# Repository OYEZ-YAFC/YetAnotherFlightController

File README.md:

# YetAnotherFlightController

Repository for the YAFC project at Université Toulouse III - Paul Sabatier, 2022-2023, Master 1 Computer Science Embedded Systems.

## Authors / Contact :

- Oussama Felfel - oussama.felfel@univ-tlse3.fr

- Yasmine Benhaddou - yasmine.benhaddou@univ-tlse3.fr

- Elana Courtines - elana.courtines@univ-tlse3.fr

- Zineb Moubarik - zineb.moubarik@univ-tlse3.fr

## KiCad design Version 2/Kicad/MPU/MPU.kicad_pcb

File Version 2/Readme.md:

# How to Setup Betaflight Firmware

----------------------------------------------------------------------------------------------------------------
## 1.Install Betaflight Configurator

### Installation & Documentation
See: https://betaflight.com/docs/wiki

### Configuration Tool
To configure Betaflight you should use the Betaflight-configurator GUI tool (Windows/OSX/Linux) which can be found here:

https://github.com/betaflight/betaflight-configurator/releases/latest
---------------------------------------------------------------------------------------------------------------

## 2.Update Firmware

Flashing the FC consists of updating it so that it can have the latest software version from the constructor.

Before performing any manipulation on your fpv drone, you must save the original data of your drone. Indeed, if you have made a bad manipulation on the configuration, you just have to go back to this basic version of your configuration.

To perform the update, you must be in DFU (bootloader) mode. To do this, go to the “CLI” and tape : version, it will show us which target we should install. After that tape the command : diff,  by using this command, you can easily see the changes you have made to your drone's configuration and compare them to a previous working configuration. This can be useful for troubleshooting configuration issues or for optimizing your drone's performance.

the last step, is to be able to flash the firmware, you will have to restart in DFU mode (bootloader).
It is also possible to launch this mode by pressing the physical button of the FC and unplugging and replugging the USB cable.

Thereafter, => click “Flash Firmware” on Betaflight’s left navigation bar.

=> disable “Show release candidates” 
=> choose the model of your card.
=> select the latest available version of your FC.
Then it remains to click on “Load firmware [Online]”.

----------------------------------------------------------------------------------------------------------------
## 3.Configure Betaflight For The First Time
----------------------------------------------------------------------------------------------------------------
##   3.1.Connect FC to Computer

----------------------------------------------------------------------------------------------------------------
##   3.2.Setup

The “Setup” tab allows you to calibrate the accelerometer of your flight controller.

An accelerometer measures the linear acceleration of the drone on 3 axes (X/Y/Z). As a result, you will be able to know if your drone is moving on one of these three axes.

To calibrate your accelerometer, you must position your chassis flat, and click on the “calibrate” button. Make sure that it is of course a flat surface and that nothing moves during the calibration.

----------------------------------------------------------------------------------------------------------------
##   3.3.Port

At this stage, you have several options:

- Assign a receiver (Rx) to a UART: in the “Serial Rx” column, check the small button (it should turn yellow). If your receiver is on UART 4 (Tx 4 and Rx 4 on your FC), you need to go to the line of UART 4 (on Betablight).
- Declare a 4-in-1 ESC to a UART (individual ESCs do not need to be assigned): in the “Sensor Input” column, choose ESC.
- Assign a VTX to a UART.
- Declare a GPS to an UART (if you have one): always in the “Sensor input” column, choose GPS.

----------------------------------------------------------------------------------------------------------------

##   3.4.Configuration

In this part of Betaflight, you will be able to configure a major part of your multirotor (ESC etc…). For this, you have a multitude of fields to complete:
“System configuration” field:

“Gyro update frequency”: this value is blocked, no need to take care of it
“PID loop frequency”: leave the original value
Disable or enable the “barometer” if your HR has it
Disable “magnetometer”

“Other features” field:

TELEMETRY: activating telemetry will allow you to retrieve information from the sensors of your Flight Controller on the remote control
AIRMODE: the airmode must be activated since it allows your drone to keep the same trajectory when you let go of the controls. This prevents it from doing 360s when you let go of the controls.
OSD: this feature must be activated to have the information in your glasses or your FPV mask

“ESC/Motor Features” field:

“ESC/motor protocol”: This is the language used to communicate from the ESC to the FC. I invite you to see the ESC product sheet. OneShot and MultiShot protocols are older compared to Dshot protocol. If you have Dshot, I invite you to choose the Dshot300 or Dshot600. If you choose higher, you risk “burning” your ESC. In the situation where your ESCs do not have this protocol, fall back on OneShot125 or even Multishot

“Arming” field:

“Maximum angle to arm“: this value must be “180°”, this will allow you to take off your drone in the situation where it is stuck on a branch at 90 degrees from the ground.

----------------------------------------------------------------------------------------------------------------
##   3.5. Power & battery
Betaflight can report the current LiPo status to the pilot, and whether or not he can continue to fly. To do this, go to the “Power and battery” tab and configure:

The “Battery” field:

“Minimum voltage per cell”: 3.75 Volt per cell, once you have reached this battery level, you must land to preserve your battery.
“Maximum voltage per element”: 4.2 Volt per cell.
“Warning voltage per cell”: 3.70 Volt per cell. Going below this value can irreversibly damage your LiPo!

----------------------------------------------------------------------------------------------------------------
##   3.6.Voltage Calibration

----------------------------------------------------------------------------------------------------------------
##   3.7.Receiver

----------------------------------------------------------------------------------------------------------------
##   3.8.Modes 

I advise you to activate the following modes:

- PREARM: the prearm constitutes an additional security for arming (activating) the motors. In the situation where you accidentally cock your drone in your hands. It can save you from unnecessary injuries.
- ARM: arming your drone consists of activating the drone's motors
- HORIZON: for beginners, this mode allows the drone to be stabilized if necessary
- BEEPER: ring the buzzer (if you have one)
- GPS RESCUE: activate the GPS (if you have one)
To do this, you must choose an “AUX” and slide the rightmost or leftmost range selector.

----------------------------------------------------------------------------------------------------------------
##   3.9.Motors

You must test your motors one by one and you have to use the white slider to spin the motor and see if there is an error. Raise this value slightly (to 1050 or 1100), there is no point in raising it too high except overheating your components.

This is also an opportunity to check if the correct motor is running. For example, if you run motor 1, motor 1 is running and so on...

----------------------------------------------------------------------------------------------------------------
##   3.10.OSD

----------------------------------------------------------------------------------------------------------------
##   3.11.PID Tuning

----------------------------------------------------------------------------------------------------------------
##   3.12.Video Transmitter

----------------------------------------------------------------------------------------------------------------
##   3.13.Expert Mode

----------------------------------------------------------------------------------------------------------------
##   3.14.Stop Beeping on the Bench

----------------------------------------------------------------------------------------------------------------
##   3.15.Safety Checks Before Maiden Flight

----------------------------------------------------------------------------------------------------------------

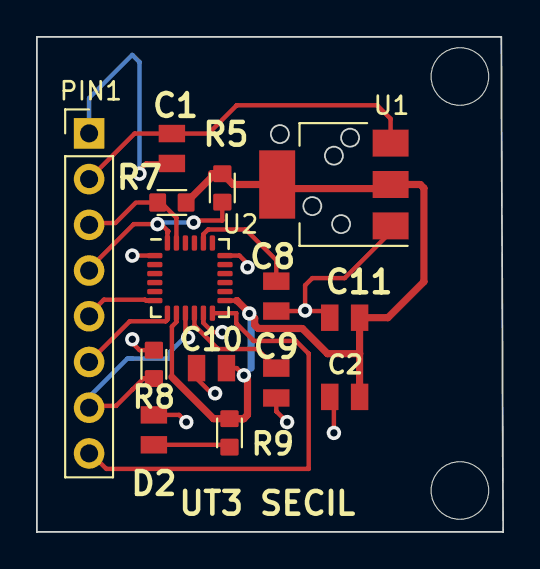
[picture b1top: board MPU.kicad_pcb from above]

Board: 2 copper layers, 25.9 x 27.5 mm, 14 parts (0 on the bottom side), 12 nets.

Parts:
C1: 4.7uF; CAPC2012X145N
C2: 10uF; CAPC2012X145N
C8: 2.2uF; CAPC2012X145N
C9, C10, C11: 100nF; CAPC2012X145N
D2: LED; CAPC2012X145N
PIN1: Conn_01x08; PinHeader_1x08_P2.54mm_Vertical
R5, R7, R8: 4.7k; RESC1608X50N
R9: 1k; RESC1608X50N
U1: AMS1117-3.3; SOT-223-3_TabPin2
U2: MPU-6050; InvenSense_QFN-24_4x4mm_P0.5mm

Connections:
+3.3V: C2.2, C10.2, C11.2, R5.1, R7.1, R9.1, U1.2 (VO), U2.8 (VLOGIC), U2.13 (VDD)
/AD0: PIN1.7, R8.2, U2.9 (AD0)
/INT: PIN1.8, U2.12 (INT)
/SCL: PIN1.3, R7.2, U2.23 (SCL)
/SDA: PIN1.4, R5.2, U2.24 (SDA)
/XCL: PIN1.6, U2.7 (AUX_CL)
/XDA: PIN1.5, U2.6 (AUX_DA)
GND: C1.1, C2.1, C8.2, C9.1, C10.1, C11.1, D2.1 (K), PIN1.1, R8.1, U1.1 (GND), U2.1 (CLKIN), U2.11 (FSYNC), U2.18 (GND)
unnamed: D2.2 (A), R9.2
unnamed: C8.1, U2.20 (CPOUT)
unnamed: C9.2, U2.10 (REGOUT)
VCC: C1.2, PIN1.2, U1.3 (VI)

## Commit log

2022-11-30 Updated: README.md - added authors
2022-11-30 Added: tex file for the kickoff
2022-11-30 Updated: Kickoff meeting presentation
    The kickoff meeting latex file has been updated. It is ready for the meeting.
2022-12-01 Updated: Kickoff presentation
    Both the LaTeX and the PDF files now reflect the most recent changes.
2022-12-05 Removed: Deliverable files have been moved elsewhere
2023-01-13 Added: first test file for ICM20948 component
    The commit contains the associated test file, wiring as follow :
    - 5v -> 2-6v
    - A5 -> SCL
    - A4 -> SDA
    - GND -> GND
    - D5 -> LED
2023-01-20 Added: new files for MPU6050
2023-01-27 Added: first code attempt of a quad motor
2023-02-03 Style : Creating folders for every version
2023-02-08 Added: code to arm the motor (warning, be cautious)
2023-02-10 Added: new motor arming test file, v1.1 automate file
2023-02-10 Added: new motor arming tests files
2023-02-10 Update: some updates to automatev1.1
2023-02-10 Update: automate v1.1 minor adjustments
2023-02-13 Update : Describing test procedure
2023-02-13 Update: Readme.md in Version 1
2023-02-17 Update: motor arming3
2023-02-17 Update: automate v1
2023-02-17 Added: motor arming 4
2023-02-24 Added: pid code for one axis
2023-03-06 Added: Readme.md in Version 0
    This file will serve as an description file for everything that has been found during this V0 investigation
2023-03-23 Added : Readme Betaflight
2023-03-23 Added : imgs
2023-04-02 new update
2023-04-15 Added: Kicad files (reorganising folders)
2023-04-18 Modified: Routing
2023-04-18 Modified: Correcting design rules errors
2023-04-18 Modified: no warning or errors detected
2023-04-18 Modified: adding title
2023-04-20 Modified: rerouting the pcb
2023-04-20 Modified: generating gerber files
2023-04-20 Added: BOM & CPL files
2023-04-24 Create LICENCE
